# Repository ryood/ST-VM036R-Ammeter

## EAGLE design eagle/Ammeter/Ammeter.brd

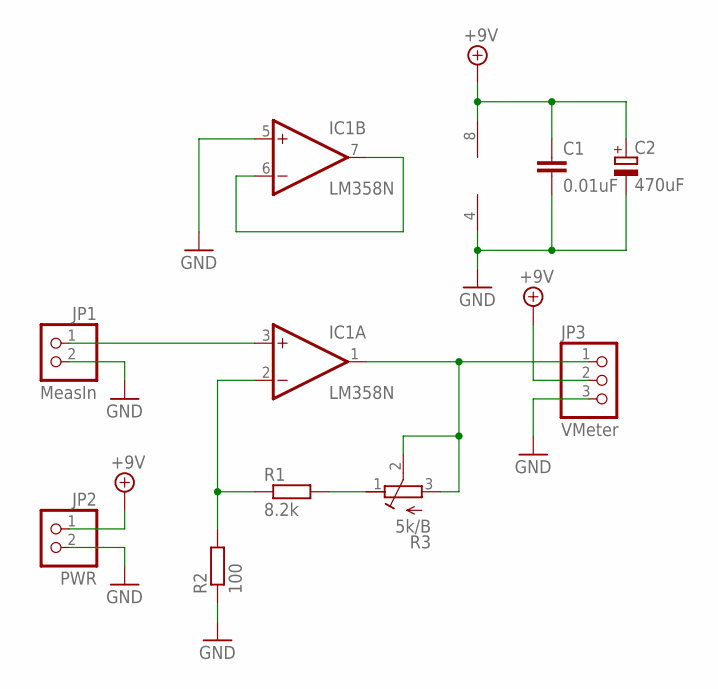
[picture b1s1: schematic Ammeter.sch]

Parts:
C1: 0.01uF; C025-024X044
C2: 470uF; SANYO-OSCON_F13
IC1: LM358N; DIL08
JP1: MeasIn; 1X02
JP2: PWR; 1X02
JP3: VMeter; 1X03
R1: 8.2k; 0207/7
R2: 100; 0207/7
R3: 5k/B; RTRIM43P

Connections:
+9V: C1.1, C2.+, IC1.8 (V+), JP2.1, JP3.2
GND: C1.2, C2.-, IC1.4 (V-), IC1.5 (+IN), JP1.2, JP2.2, JP3.3, R2.1
unnamed: IC1.3 (+IN), JP1.1
unnamed: IC1.2 (-IN), R1.1, R2.2
unnamed: IC1.1 (OUT), JP3.1, R3.2 (S), R3.3 (A)
unnamed: R1.2, R3.1 (E)
unnamed: IC1.6 (-IN), IC1.7 (OUT)

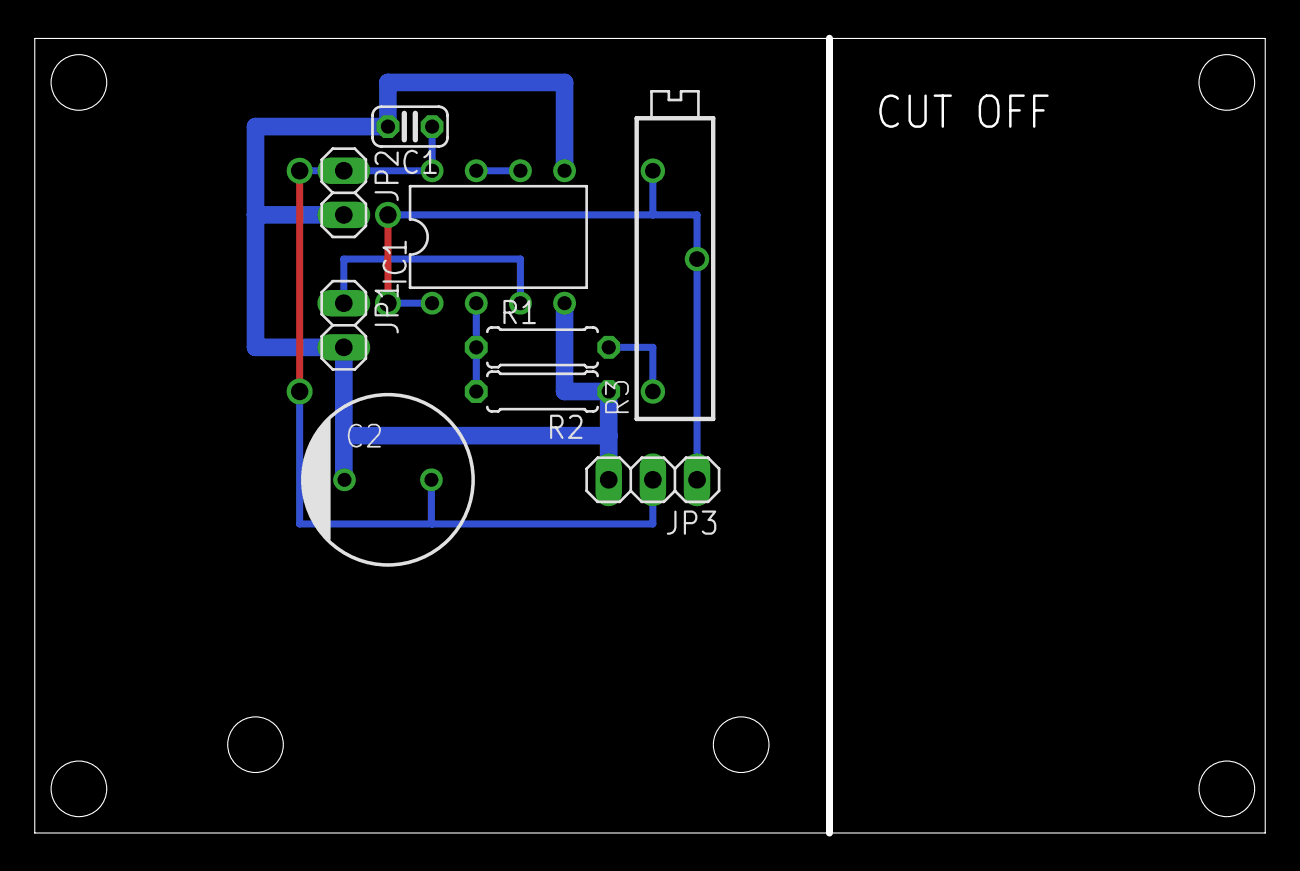
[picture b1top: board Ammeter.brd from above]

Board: 2 copper layers, 70.4 x 45.7 mm, 9 parts (0 on the bottom side), 7 nets.

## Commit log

2017-02-01 Add: 精度測定
